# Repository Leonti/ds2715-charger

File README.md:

FK3503010L - N-channel  
IRLML2246TRPBF - P-channel

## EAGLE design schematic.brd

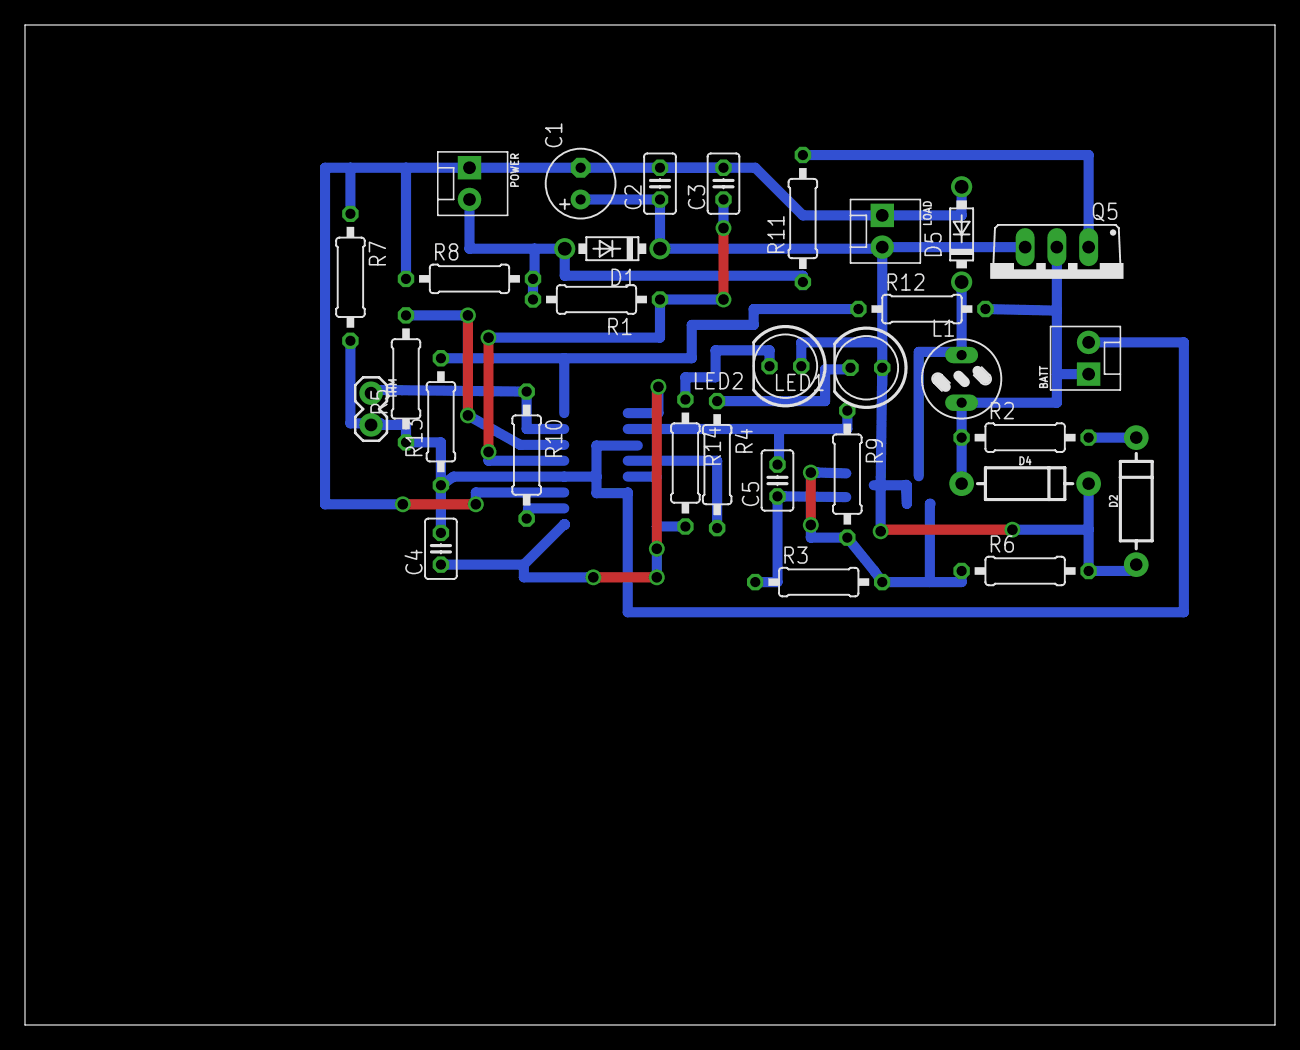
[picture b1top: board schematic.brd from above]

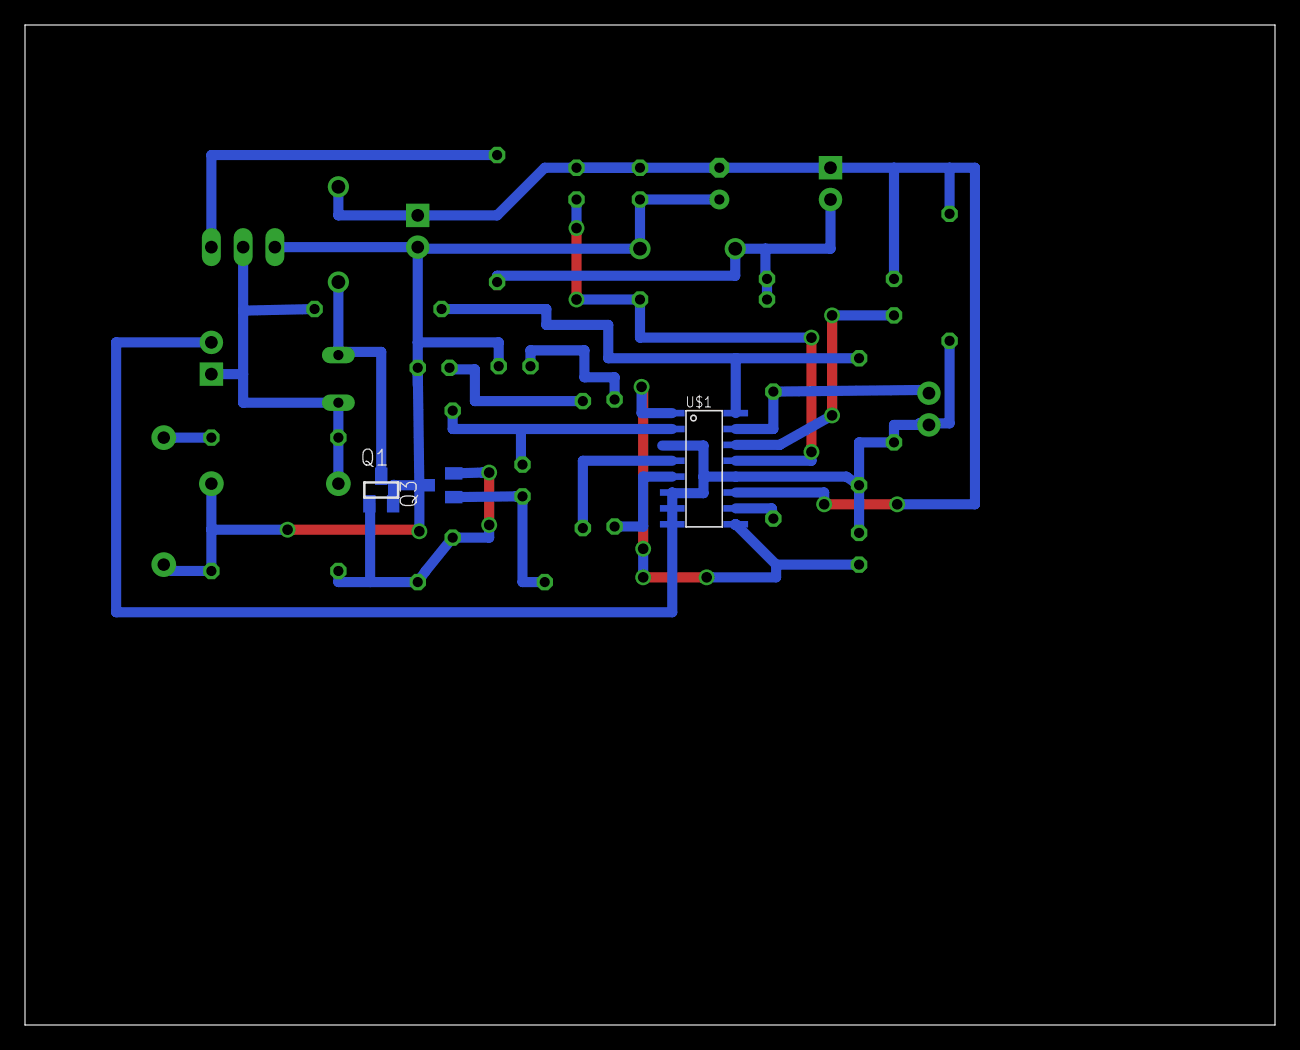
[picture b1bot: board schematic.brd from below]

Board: 2 copper layers, 100.0 x 80.0 mm, 34 parts (3 on the bottom side), 21 nets.

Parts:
BATT: MOLEX-1X2
C1: 47uF; E2,5-6
C2: 1uF; C025-025X050
C3, C4: 0.1uF; C025-025X050
C5: 1nF; C025-025X050
D1, D5: 1N5817-B; DO41-7.6
D2, D4: 1A/50V/1.1V; DIODE-1N4001
L1: 82114R
LED1, LED2: LED5MM
LOAD: MOLEX-1X2
POWER: MOLEX-1X2
Q1: FDN360P; SUPER-SOT3
Q3: BSS123; SOT23
Q5: TO220BV
R1: 150; 0207/10
R2: 220; 0207/10
R3: 820; 0207/10
R4, R14: 1k; 0207/10
R5: 160k; 0207/10
R6: 330; 0207/10
R7: 0.1; 0207/10
R8, R13: 100k; 0207/10
R9: 470; 0207/10
R10: 10k; 0207/10
R11: 100; 0207/10
R12: 500k; 0207/10
THM: 1X02
U$1: DS2715; DS2715-SO16

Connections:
GND: C1.-, C2.2, C3.2, D5.A, LOAD.1, POWER.1, R7.1, R8.1, U$1.11
unnamed: Q5.G, R11.2
unnamed: LED2.K, R14.1
unnamed: R14.2, U$1.5
unnamed: BATT.2, C4.2, R5.1, R7.2, R13.1, THM.2, U$1.3, U$1.6, U$1.7, U$1.8, U$1.12
unnamed: R10.1, THM.1, U$1.15
unnamed: R10.2, U$1.10
unnamed: R12.1, R13.2, U$1.16
unnamed: BATT.1, D4.A, L1.2, Q5.D, R2.1, R12.2
unnamed: R4.2, U$1.4
unnamed: D5.C, L1.1, Q1.3
unnamed: C5.2, R9.1, U$1.2
unnamed: Q1.1, Q3.2, R3.2, R6.1, R9.2
unnamed: C5.1, Q3.1, R3.1
unnamed: LED1.K, R4.1
unnamed: D2.C, R2.2
unnamed: C3.1, R1.1, U$1.13
unnamed: R5.2, U$1.14
unnamed: C4.1, U$1.1, U$1.9
unnamed: D1.A, POWER.2, R1.2, R8.2, R11.1
unnamed: C1.+, C2.1, D1.C, D2.A, D4.C, LED1.A, LED2.A, LOAD.2, Q1.2, Q3.3, Q5.S, R6.2

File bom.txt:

Partlist exported from /home/leonti/eagle/DS2715/schematic.sch at 21/05/2017 11:47

Qty Value       Device           Package      Parts             Description                                                                                                     PROD_ID   SF_ID     VALUE      
1               CONN_02          1X02         THM               Multi connection point. Often used as Generic Header-pin footprint for 0.1 inch spaced/style header connections                                
3               CONN_02POLAR     MOLEX-1X2    BATT, LOAD, POWER Multi connection point. Often used as Generic Header-pin footprint for 0.1 inch spaced/style header connections           PRT-09918            
1               LED5MM           LED5MM       LED1              LED                                                                                                                                            
2               PMOSFET_PTO220BV TO220BV      Q1, Q5            Power MOSFET P-Channel                                                                                                                         
1   0.1         R-EU_0207/10     0207/10      R7                RESISTOR, European symbol                                                                                                                      
2   0.1uF       C-EU025-025X050  C025-025X050 C3, C4            CAPACITOR, European symbol                                                                                                                     
1   100         R-EU_0207/10     0207/10      R11               RESISTOR, European symbol                                                                                                                      
2   100k        R-EU_0207/10     0207/10      R8, R13           RESISTOR, European symbol                                                                                                                      
1   10k         R-EU_0207/10     0207/10      R10               RESISTOR, European symbol                                                                                                                      
1   150         R-EU_0207/10     0207/10      R1                RESISTOR, European symbol                                                                                                                      
1   160k        R-EU_0207/10     0207/10      R5                RESISTOR, European symbol                                                                                                                      
2   1A/50V/1.1V DIODE-PTH        DIODE-1N4001 D2, D4            Diode                                                                                                           DIO-09176           1A/50V/1.1V
2   1N5817-B    1N5817-B         DO41-7.6     D1, D5            1.0A SCHOTTKY BARRIER RECTIFIER                                                                                                                
1   1k          R-EU_0207/10     0207/10      R4                RESISTOR, European symbol                                                                                                                      
1   1nF         C-EU025-025X050  C025-025X050 C5                CAPACITOR, European symbol                                                                                                                     
1   1uF         C-EU025-025X050  C025-025X050 C2                CAPACITOR, European symbol                                                                                                                     
1   220         R-EU_0207/10     0207/10      R2                RESISTOR, European symbol                                                                                                                      
1   330         R-EU_0207/10     0207/10      R6                RESISTOR, European symbol                                                                                                                      
1   470         R-EU_0207/10     0207/10      R9                RESISTOR, European symbol                                                                                                                      
1   47uF        CPOL-EUE2.5-6    E2,5-6       C1                POLARIZED CAPACITOR, European symbol                                                                                                           
1   500k        R-EU_0207/10     0207/10      R12               RESISTOR, European symbol                                                                                                                      
1   820         R-EU_0207/10     0207/10      R3                RESISTOR, European symbol                                                                                                                      
1   82114R      82114R           82114R       L1                INDUCTOR                                                                                                                                       
1   DS2715      DS2715           DS2715-SO16  U$1                                                                                                                                                              
1   IRF540      IRF540           TO220BV      Q3                HEXFET Power MOSFET

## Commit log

2017-05-17 Create connections
2017-05-17 Place elements a bit better
2017-05-18 Improve placement of elements
2017-05-18 Btter layout
2017-05-18 Further improvements
2017-05-19 start drawing the board
2017-05-20 Layout done
2017-05-21 Create pdf with pcb
2017-05-28 Latest version
2017-05-29 Add new board
2017-05-30 Preliminary component position
2017-05-30 Improved routing
2019-12-01 Add new pdf for printing

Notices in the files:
parts and their libraries:
SparkFun-Connectors: Licensing: Creative Commons ShareAlike 4.0 International - https://creativecommons.org/licenses/by-sa/4.0
